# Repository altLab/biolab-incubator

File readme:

Kicad Drawings for an incubator based on https://www.instructables.com/Incubadora-Garagem-FabLab-Biohackacademy/

#Version 1.1

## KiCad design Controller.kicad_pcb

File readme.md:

Kicad Drawings for an incubator based on

https://www.instructables.com/Incubadora-Garagem-FabLab-Biohackacademy/

# Information

The kicad drawings don't have real footprint assignment, they are first proposal with real components, but never have been fabricated

They are only for rendering purposes

Consider it a **WIP** stage

# Version 1.0

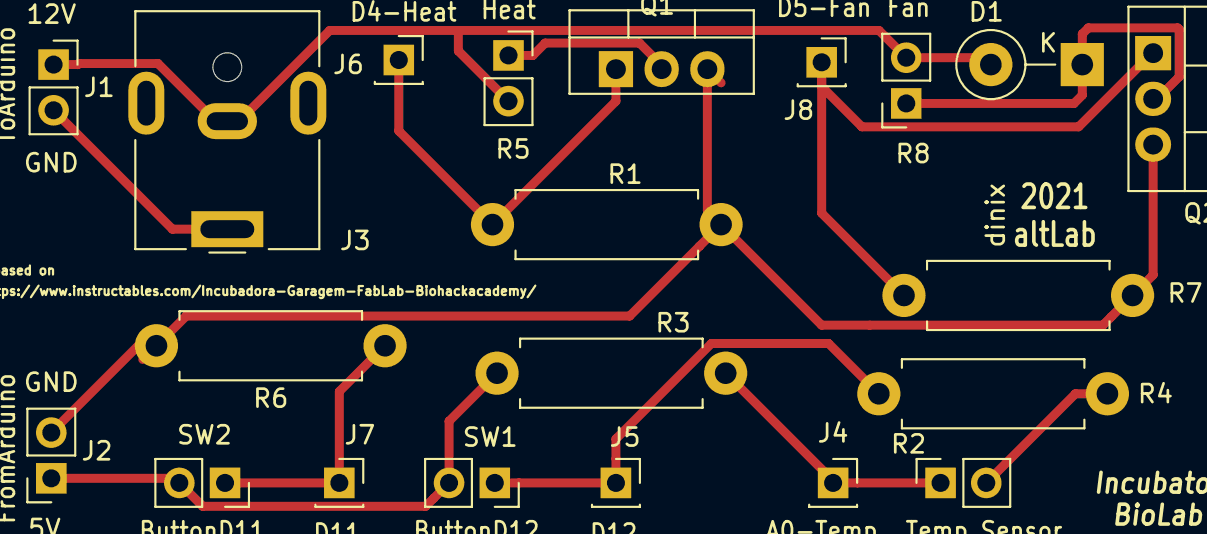
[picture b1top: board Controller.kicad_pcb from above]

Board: 2 copper layers, 21 parts (0 on the bottom side), 11 nets.

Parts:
D1: DIODE; D_DO-15_P5.08mm_Vertical_KathodeUp
J1: ToArduino; PinSocket_1x02_P2.54mm_Vertical
J2: FromArduino; PinSocket_1x02_P2.54mm_Vertical
J3: Power12V; BarrelJack_CUI_PJ-063AH_Horizontal
J4: A0 Sensor; PinSocket_1x01_P2.54mm_Vertical
J5: D12; PinSocket_1x01_P2.54mm_Vertical
J6: D4 - Heat; PinSocket_1x01_P2.54mm_Vertical
J7: D11; PinSocket_1x01_P2.54mm_Vertical
J8: D5-Fan; PinSocket_1x01_P2.54mm_Vertical
Q1: IRF-Heat; TO-220-3_Vertical
Q2: IRF-Fan; TO-220-3_Vertical
R1: Heat-R; R_Axial_DIN0411_L9.9mm_D3.6mm_P12.70mm_Horizontal
R2: Sensor; PinSocket_1x02_P2.54mm_Vertical
R3: Temp R; R_Axial_DIN0411_L9.9mm_D3.6mm_P12.70mm_Horizontal
R4: Pull-D12; R_Axial_DIN0411_L9.9mm_D3.6mm_P12.70mm_Horizontal
R5: Heating; PinSocket_1x02_P2.54mm_Vertical
R6: Pull-D11; R_Axial_DIN0411_L9.9mm_D3.6mm_P12.70mm_Horizontal
R7: Fan-R; R_Axial_DIN0411_L9.9mm_D3.6mm_P12.70mm_Horizontal
R8: Fan; PinSocket_1x02_P2.54mm_Vertical
SW1: Button +; PinSocket_1x02_P2.54mm_Vertical
SW2: Button -; PinSocket_1x02_P2.54mm_Vertical

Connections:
unnamed: D1.1, Q2.2, R8.1
unnamed: D1.2, J1.1, J3.2, R5.2, R8.2
unnamed: J1.2, J3.1
unnamed: J2.1, R3.1, SW1.2, SW2.2
unnamed: J2.2, Q1.3, Q2.3, R1.2, R2.2, R4.2, R6.2, R7.2
unnamed: J4.1, R2.1, R3.2
unnamed: J5.1, R4.1, SW1.1
unnamed: J6.1, Q1.1, R1.1
unnamed: J7.1, R6.1, SW2.1
unnamed: J8.1, Q2.1, R7.1
unnamed: Q1.2, R5.1

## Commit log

2021-05-26 V1 Initial Load
2021-05-29 version 1.1 #4 #5
2021-05-30 readme update references
